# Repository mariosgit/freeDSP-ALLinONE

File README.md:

# freeDSP ALLinONE
BOARD STATUS: READY TO BE BUILT

Upgrade of the [freeDSP Classic SMD-B](https://github.com/freeDSP/freeDSP-CLASSIC-SMD-B/blob/master/README.md)

LICENCE: Creative Commons Attribution Share-Alike 4.0 license

https://freedsp.github.io/

[Mouser BOM](https://www.mouser.com/ProjectManager/ProjectDetail.aspx?AccessID=5c5f7288d7)

## mb/improvements branch

 * PowerDown muting, implemented with one 7414 gate and a Pot. The Pot must be fully turned up (cw) and then down until the mute LED turns of. This determines the Vin voltage where the shutdown occures, it should be slightly below the supply voltage but higher then 5V because @5V the Amps will go into power fail and that will hard click. [simulation](https://www.falstad.com/circuit/circuitjs.html?ctz=CQAgjCAMB0l3BWEAmM0EE4DMGAcB2ZLMSANjABYxkQFTbbJaBTAWjDACgA3EV-XBXCkmrQbmFMmEElOgQpUdJwBKfcZPUZ6YEVHAppNavpgJOAB3W6UyIWJvJcErKc5hcr1lgTH89VmRCcH9TdHBoUnosaCxXJEh3Tz4fGm0+ILT6OSQ0KJAYuIZEjy9UkAo4DODKxTMI-ML4qE4Adz4wUJt2ExtE9sC7YQ6u7M4AcxH6XFFO+nSpTgBjKeH2UJn9ZDYJCmgMASxPQWQ8OiclOC4AJ1XWCgl1nWzweDg21bn1aVDE26eQgEvnZFLJ4MtViDVlhIEImNsxBV9lgHnhnARSMhThhLpAuJMATD7F8sMg6h9BkIoQCof1IZUOiZaRSvl9AsEvnTKWtyn0KbyAuUFpZqjRaqKKqQhK5FlYemKqvLJdK3ANMiB0uzjBcuerqI9eTr+b5wBdvCbORSsVSGeaaMyBuVqeVxYkyfgOvRXQUsF6QABbACuABdmJx3RK2WSJJQhEIAIL+iysAD0AFEAHLhyAehzPUTOJgPCogABqAEsAHYACmogQopYAlNnc4R4bbMUIOGKAwBDCwAHQAzkPAxYLAAbACew9Lw+DAHthwhSxTcI4hnnNH8+G2ULa90T9DN3gTD7Dd2SClfFgM99TSHR97K+I-6A+n0eZS1SnwEKFqQodJaSUXJImiWJmi5e9IEee8GUSOUgPfW1kIqKpv11IYj0JC8sKpYJuWZX97lJPhiztciJByBoIKKBIRSValuwKC9MONGh7keNliy5CgyMAsiuJaAY2X1O5eM4AATCVxXYDAFXhEApOYAAzXtAwnYNpNkzUwAUipgOUtSNK0lkTDk-TFJEjoDMsuzhQGfixU1ZznxaOUpSo19pRodiBi84SAWEt0czucSgt0IsQAABQXVpmGuAB5SsWxSE0gpw9IhAAK0DIdg2HXthwAC2YCcLES+clyHcZmEKodClXCNWH-FDRF8GNQiEct-X9ZgpPLXtQ2HCx4qqocpPiythxU0MlmDcsF1SlqrMMgJNgQCg4xAJKVGHBdVNG8brim1oZqHAAfY6EuuMc0uCijNlYbKQCHCd4puiax1m+rmAWpbUv+N93NagCENed4nOA1CBIQ9xMU9dDZi9TYaBU9TNODVgJwGgwFEufEkYeFH1rcf4bEsiyqiYBAofIsi0K1MnoKvFj+EEcATGgzn2YELs9BKfB7D3PnSBjAyIDp+BLgwKg3gV+AaBUZgh3LAre0rJYwzvcXNA5gXFha9U5OjAoTSECwq1IYcq2HVTrmYAahwsTgF0Ma99AAD3XPEaASeR9CQJAJFQIO-yEBACaQCh330EhaD86iGECLA3YqPyaCYH2SCZOQZBLBJzfj8ixW-JBvDLgpLgYoA)
 * One of the 7414 was redundand and has been removed.
 * One of the clip adjust pots was redundand and has been removed.
 * 5V Arduino port was removed, use a 3.3 V device, i2C on the freedsp and adau headers.
 * Added a MCP23008 to read status and provide mute and spdif switching control. Can be left out.
 * I had problems with the ADAU onboard voltage regulator, replaced it with a linear regulator. (dropout is 1.2V should be ok to run @ 3.3V) Anyway increased the switched reg to 5V and the 3.3V line runs on another 1117.
 * Ferritbead before the AMP chips is wrong, AMPs are now powered by VIN.
 * Removed Power input from USBi port.
 * JumperWire and solder enforceable power traces between amps and power terminal
 * break out gain config pins - add 1k resistors r49 r50 as needed.

##### CanDo ?

 * Replace CS8422 QFPpamp / Outdated. But it's the only one with integrated SRC :( 
 * Replace 1206 parts with std 603 parts.
 * Use a power management/supervisor chipo for mute ? 
   * TPS3840PH49DBVR ? ActHigh not adjustable, max 12v
   * TL7700 - active low
   * TPS38 - availables are active low.
   * TL7733 - max 20V, act low+high
   * aaahhh

## About

The freeDSP is an open-source digital signal processor family for the do-it-yourself community. The applications range from active loudspeaker concepts (digital crossovers, bass enhancement, ...) and room equalization over advanced musical effect processors to car audio signal processing. 

The _freeDSP ALLinONE_ is an all-in-one version of the original _freeDSP Classic SMD-B_ with a few improvements, upgrades and changes.
It features four amplified analog outputs as well as S/PDIF in- and output (optical and RCA).
This board has been designed using the Cross-Platform Open Source Tool [KiCad](http://kicad.org/).

More informations kann be found on the [freeDSP website](http://freedsp.cc)

You can find a PDF version of the schematic in the SOURCES folder (LINK)

## Links

[freeDSP Website](http://freedsp.cc)

[Documentation in Google Doc](https://docs.google.com/document/d/1258PKKEvrk1GpFIaAHhm8G6f0HHNBfSL8KVq2VGgUKc/edit?usp=sharing)

[freeDSP Guidelines](https://github.com/freeDSP/WIKI-AND-GENERAL-TOPICS/wiki/freeDSP-Guidelines)

## Git usage

#### How to setup local repository
- Change to your FreeDSP directory
- Clone the repository (including submodule)  
 `git clone --recursive https://github.com/freeDSP/freeDSP-ALLinONE.git` 
- Change to the newly created ALLinONE directory
- Checkout a branch for the library submodule, if you want to modify it as well
  `git submodule foreach 'git checkout 'master''`
- Open the project file in KiCad

#### How to update the local copy
- To update the project  
  `git pull`
- To update the library  
  `git submodule update --remote --merge`

#### To commit and push local changes
- If you modified something in the LIBRARY folder, change to the LIBRARY folder and run  
  `git add .` (Only required if files were added)  
  `git commit -am "Message"`  (Describe what you changed)  
- Change to the project root directory and run
  `git add .` (Only required if files were added)  
  `git commit -am "Message"`  (Describe what you changed)    
- In the project directory run  
  `git push --recurse-submodule=on-demand`  

#### Define alias to make things shorter
- In the project directory run
  `git config alias.supdate 'submodule update --remote --merge'`  
  `git config alias.spush 'push --recurse-submodules=on-demand'`  
- Afterwards you can use `git supdate` to update the submodule and `git spush` to push any commited changes  

#### Other useful commands
- `git status`  
  Shows general information about the current branch, uncommited changes, not yet added new files and more
- `git diff`  
  Shows uncommited changes
- `git reset --hard origin/master`
  Reset all files to the current status of the dev-hs-01 branch on the Github repository  
  **Careful** This deletes all local changes, so make sure all changes you made and you do not want to delete are pushed to the remote repository

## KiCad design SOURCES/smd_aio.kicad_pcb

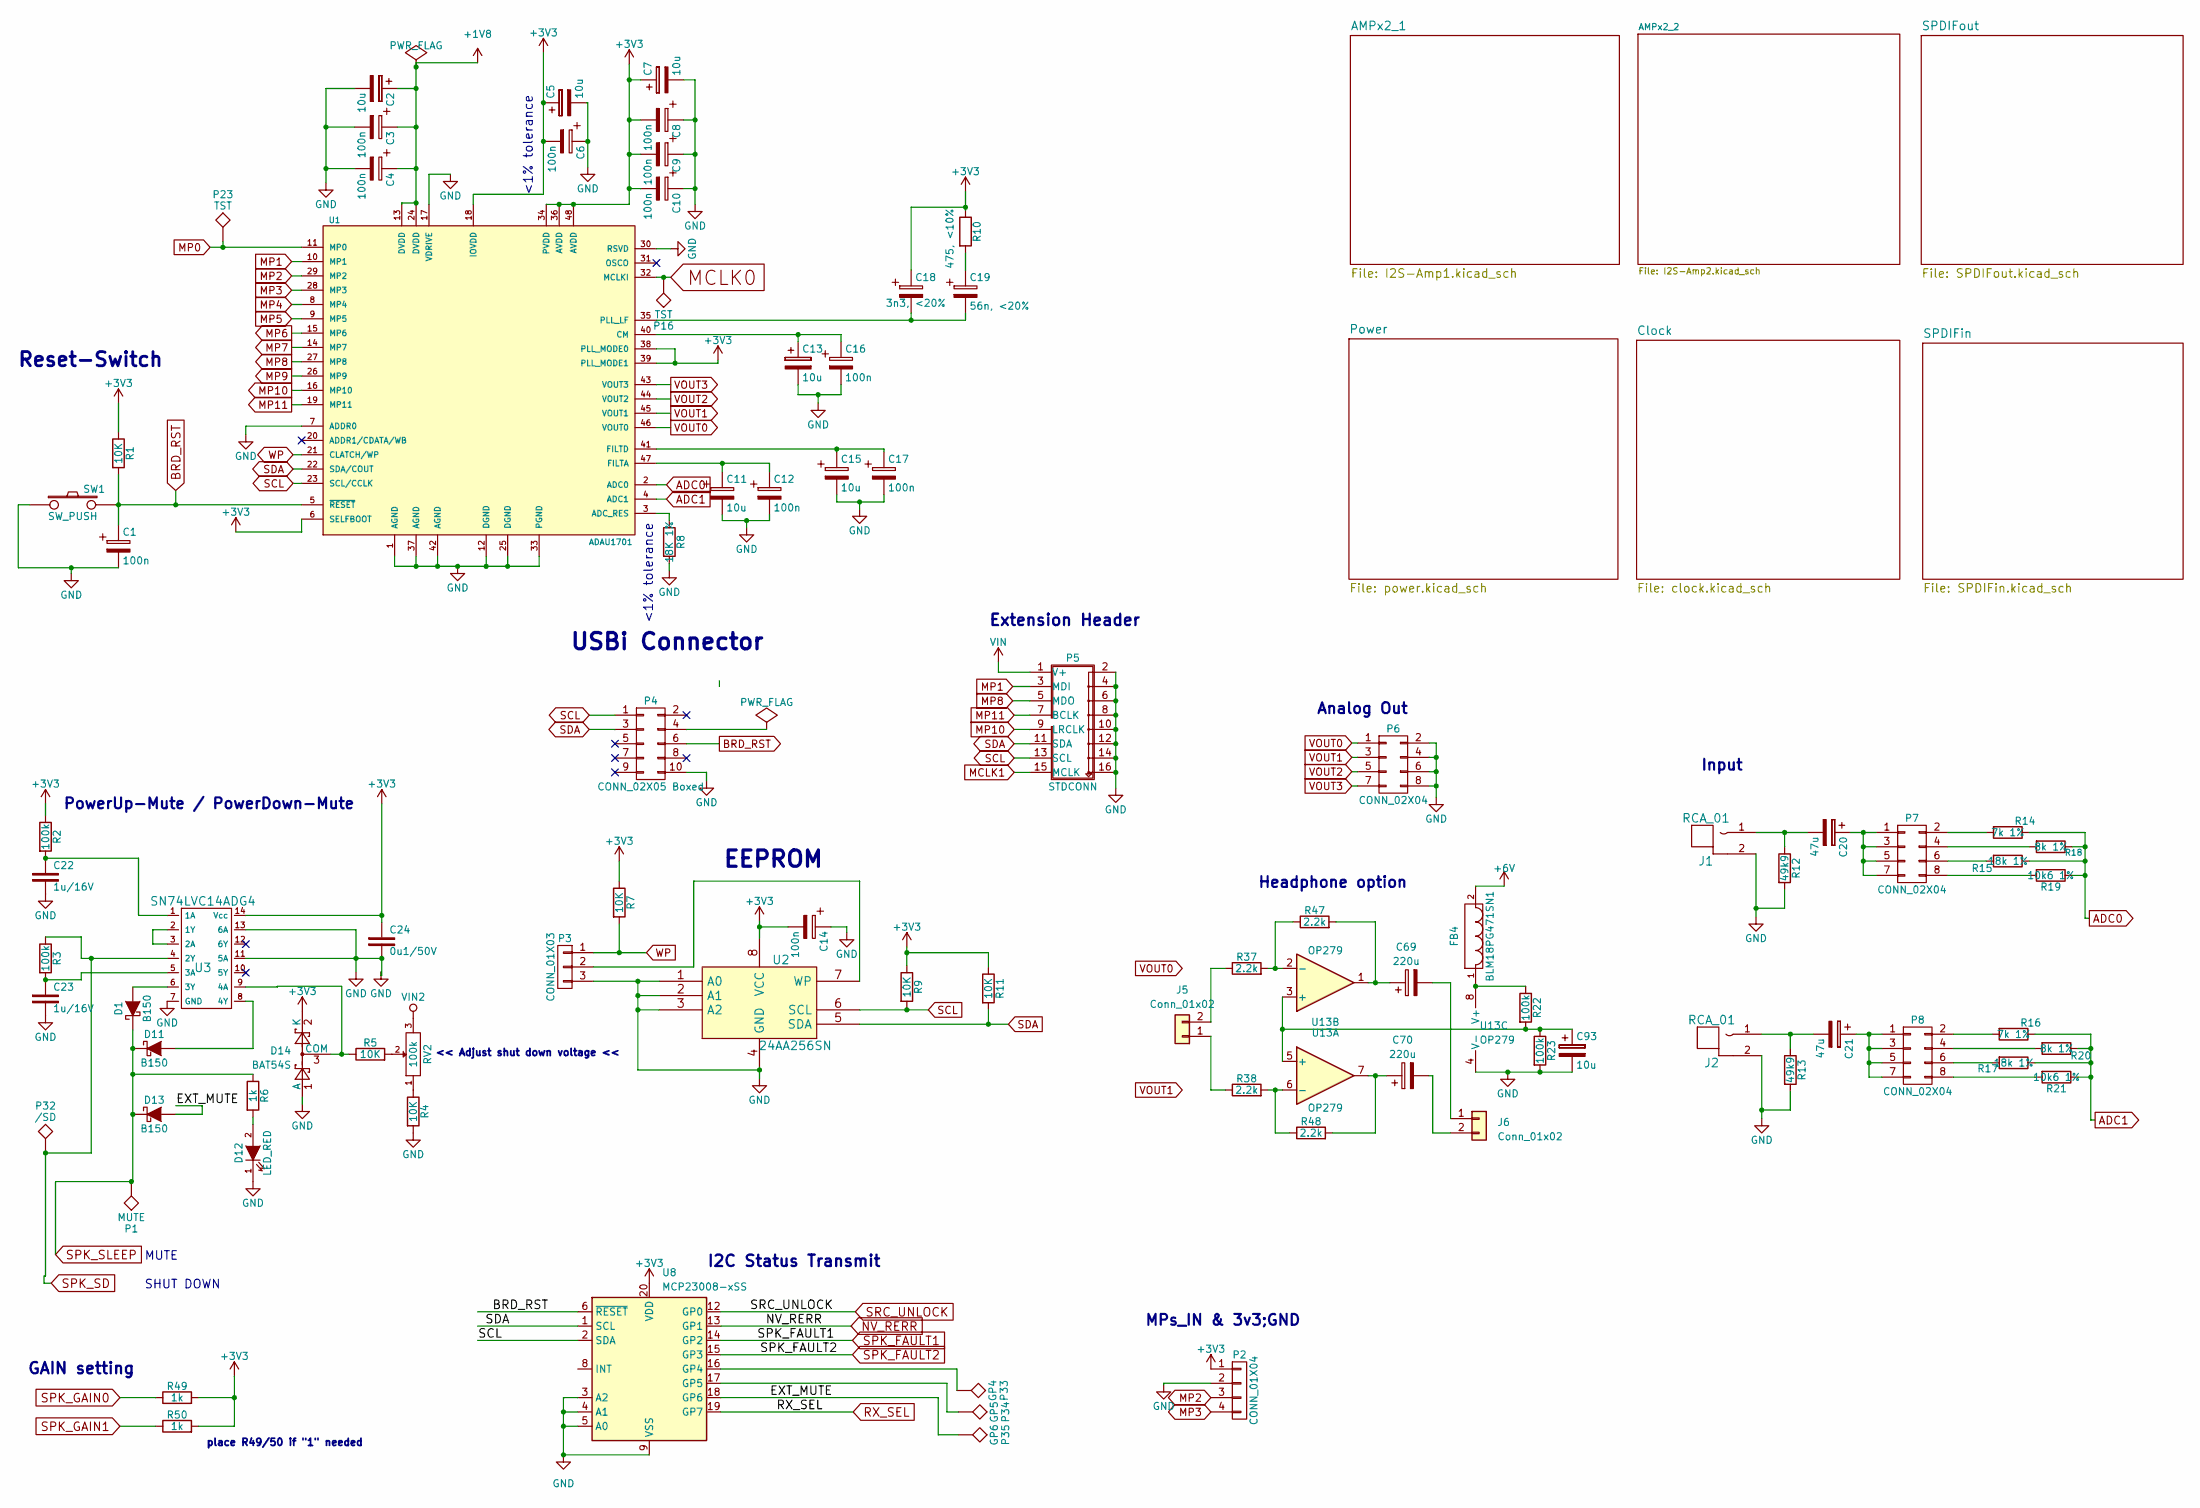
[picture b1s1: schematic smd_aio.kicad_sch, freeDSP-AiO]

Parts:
C1, C3, C4, C6, C8, C9, C10, C12, C14, C16, C17: 100n; C_1206_HandSoldering
C2: 10u; C_1210_3225Metric_Pad1.33x2.70mm_HandSolder
C5, C7, C13, C93: 10u; C_Radial_D5_L11_P2
C11, C15: 10u; C_1206_HandSoldering
C18: 3n3, <20%; C_1206_HandSoldering
C19: 56n, <20%; C_1206_HandSoldering
C20, C21: 47u; C_Radial_D5_L11_P2
C22, C23: 1u/16V; C_1206_HandSoldering
C24: 0u1/50V; C_1206_HandSoldering
C69, C70: 220u; CP_Elec_6.3x5.9
D1, D11, D13: B150; SMA
D12: LED_RED; R_1206_HandSoldering
D14: BAT54S; SOT-23
FB4: BLM18PG471SN1; R_0603_HandSoldering
J1, J2: RCA_01; RCA_RCJ-01x
J5, J6: Conn_01x02; PinHeader_1x02_P2.54mm_Vertical
P1: MUTE; Measurement_Point_Round-SMD-Pad_Small
P2: CONN_01X04; Pin_Header_Straight_1x04
P3: CONN_01X03; Pin_Header_Straight_1x03
P4: CONN_02X05 Boxed; IDC_Header_Straight_10pins
P5: STDCONN; IDC_Header_Straight_16pins
P6, P7, P8: CONN_02X04; Pin_Header_Straight_2x04
P16, P23: TST; Measurement_Point_Round-SMD-Pad_Small
P32: /SD; Measurement_Point_Round-SMD-Pad_Small
P33: GP4; Measurement_Point_Round-SMD-Pad_Small
P34: GP5; Measurement_Point_Round-SMD-Pad_Small
P35: GP6; Measurement_Point_Round-SMD-Pad_Small
R1, R4, R5, R7, R9, R11: 10K; R_1206_HandSoldering
R2, R3: 100k; R_1206_HandSoldering
R6: 1k; R_1206_HandSoldering
R8: 18K 1%; R_1206_HandSoldering
R10: 475, <10%; R_1206_HandSoldering
R12, R13: 49k9; R_1206_HandSoldering
R14, R16: 7k 1%; R_1206_HandSoldering
R15, R17: 18k 1%; R_1206_HandSoldering
R18, R20: 8k 1%; R_1206_HandSoldering
R19, R21: 10k6 1%; R_1206_HandSoldering
R22, R23: 100k; R_0603_HandSoldering
R37, R38, R47, R48: 2.2k; R_0603_HandSoldering
R49, R50: 1k; R_0603_1608Metric_Pad0.98x0.95mm_HandSolder
RV2: 100k; M64Z104KB40
SW1: SW_PUSH; SW_PUSH_6mm
U1: ADAU1701; LQFP-48_7x7mm_Pitch0.5mm
U2: 24AA256SN; SOIC-8_3.9x4.9mm_Pitch1.27mm
U3: SN74LVC14ADG4; SOIC-14_3.9x8.7mm_Pitch1.27mm
U8: MCP23008-xSS; SSOP-20_5.3x7.2mm_P0.65mm
U13: OP279; SO-8_3.9x4.9mm_P1.27mm

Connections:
+1V8: C2.1, C3.1, C4.1, U1.13 (DVDD), U1.24 (DVDD); also elsewhere on the board
+3V3: C5.1, C6.2, C7.1, C8.2, C9.2, C10.2, C14.2, C18.1, C24.1, D14.2 (K), P2.1, R1.1, R2.1, R7.1, R9.1, R10.1, R11.1, R49.2, R50.2, U1.6 (SELFBOOT), U1.18 (IOVDD), U1.34 (PVDD), U1.36 (AVDD), U1.38 (PLL_MODE0), U1.39 (PLL_MODE1), U1.48 (AVDD), U2.8 (VCC), U3.14 (Vcc), U8.20 (VDD); also elsewhere on the board
+6V: FB4.2; also elsewhere on the board
/EXT_MUTE: D13.2 (A), P35.1, U8.18 (GP6)
ADC0: R14.1, R15.1, R18.1, R19.1, U1.2 (ADC0)
ADC1: R16.1, R17.1, R20.1, R21.1, U1.4 (ADC1)
BRD_RST: C1.1, P4.6, R1.2, SW1.2, U1.5 (~RESET), U8.6 (~RESET); also elsewhere on the board
GND: C1.2, C2.2, C3.2, C4.2, C5.2, C6.1, C7.2, C8.1, C9.1, C10.1, C11.2, C12.2, C13.2, C14.1, C15.2, C16.2, C17.2, C22.2, C23.2, C24.2, C93.2, D12.1 (K), D14.1 (A), J1.2 (GND), J2.2 (GND), P2.2, P3.3, P4.10, P5.2 (GND), P5.4 (GND), P5.6 (GND), P5.8 (GND), P5.10 (GND), P5.12 (GND), P5.14 (GND), P5.16 (GND), P6.2, P6.4, P6.6, P6.8, R4.2, R8.2, R12.2, R13.2, R23.2, SW1.1, U1.1 (AGND), U1.7 (ADDR0), U1.12 (DGND), U1.17 (VDRIVE), U1.25 (DGND), U1.30 (RSVD), U1.33 (PGND), U1.37 (AGND), U1.42 (AGND), U2.1 (A0), U2.2 (A1), U2.3 (A2), U2.4 (GND), U3.7 (GND), U3.11 (5A), U3.13 (6A), U8.3 (A2), U8.4 (A1), U8.5 (A0), U8.9 (VSS), U13.4 (V-); also elsewhere on the board
MCLK0: P16.1, U1.32 (MCLKI); also elsewhere on the board
MCLK1: P5.15 (MCLK); also elsewhere on the board
MP0: P23.1, U1.11 (MP0); also elsewhere on the board
MP1: P5.3 (MDI), U1.10 (MP1)
MP2: P2.3, U1.29 (MP2)
MP3: P2.4, U1.28 (MP3)
MP4: U1.8 (MP4); also elsewhere on the board
MP5: U1.9 (MP5); also elsewhere on the board
MP6: U1.15 (MP6); also elsewhere on the board
MP7: U1.14 (MP7); also elsewhere on the board
MP8: P5.5 (MDO), U1.27 (MP8)
MP9: U1.26 (MP9); also elsewhere on the board
MP10: P5.9 (LRCLK), U1.16 (MP10); also elsewhere on the board
MP11: P5.7 (BCLK), U1.19 (MP11); also elsewhere on the board
NV_RERR: U8.13 (GP1); also elsewhere on the board
unnamed: C19.1, R10.2
unnamed: C69.1, R47.2, U13.1
unnamed: C70.1, R48.2, U13.7
unnamed: D1.2 (A), U3.6 (3Y)
unnamed: D11.2 (A), U3.8 (4Y)
unnamed: D12.2 (A), R6.2
unnamed: D14.3 (COM), R5.1, U3.9 (4A)
unnamed: C20.2, J1.1 (SIG), R12.1
unnamed: C21.2, J2.1 (SIG), R13.1
unnamed: J5.1, R38.1
unnamed: J5.2, R37.1
unnamed: C69.2, J6.1
unnamed: C70.2, J6.2
unnamed: P3.2, U2.7 (WP)
unnamed: C20.1, P7.1, P7.3, P7.5, P7.7
unnamed: P7.2, R14.2
unnamed: P7.4, R18.2
unnamed: P7.6, R15.2
unnamed: P7.8, R19.2
unnamed: C21.1, P8.1, P8.3, P8.5, P8.7
unnamed: P8.2, R16.2
unnamed: P8.4, R20.2
unnamed: P8.6, R17.2
unnamed: P8.8, R21.2
unnamed: R4.1, RV2.1
unnamed: R5.2, RV2.2
unnamed: R8.1, U1.3 (ADC_RES)
unnamed: C13.1, C16.1, U1.40 (CM)
unnamed: C11.1, C12.1, U1.47 (FILTA)
unnamed: C15.1, C17.1, U1.41 (FILTD)
unnamed: C18.2, C19.2, U1.35 (PLL_LF)
unnamed: C22.1, R2.2, U3.1 (1A)
unnamed: U3.2 (1Y), U3.3 (2A)
unnamed: C23.1, R3.2, U3.5 (3A)
unnamed: P33.1, U8.16 (GP4)
unnamed: P34.1, U8.17 (GP5)
unnamed: C93.1, R22.2, R23.1, U13.3 (+), U13.5 (+)
unnamed: R37.2, R47.1, U13.2 (-)
unnamed: R38.2, R48.1, U13.6 (-)
unnamed: FB4.1, R22.1, U13.8 (V+)
RX_SEL: U8.19 (GP7); also elsewhere on the board
SCL: P4.1, P5.13 (SCL), R9.2, U1.23 (SCL/CCLK), U2.6 (SCL), U8.2 (SDA)
SDA: P4.3, P5.11 (SDA), R11.2, U1.22 (SDA/COUT), U2.5 (SDA), U8.1 (SCL)
SPK_FAULT1: U8.14 (GP2); also elsewhere on the board
SPK_FAULT2: U8.15 (GP3); also elsewhere on the board
SPK_GAIN0: R49.1; also elsewhere on the board
SPK_GAIN1: R50.1; also elsewhere on the board
SPK_SD: P32.1, R3.1, U3.4 (2Y); also elsewhere on the board
SPK_SLEEP: D1.1 (K), D11.1 (K), D13.1 (K), P1.1, R6.1; also elsewhere on the board
SRC_UNLOCK: U8.12 (GP0); also elsewhere on the board
VIN: P5.1 (V+); also elsewhere on the board
VIN2: RV2.3; also elsewhere on the board
VOUT0: P6.1, U1.46 (VOUT0)
VOUT1: P6.3, U1.45 (VOUT1)
VOUT2: P6.5, U1.44 (VOUT2)
VOUT3: P6.7, U1.43 (VOUT3)
WP: P3.1, R7.2, U1.21 (CLATCH/WP)

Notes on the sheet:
MPs_IN & 3v3;GND
Headphone option
PowerUp-Mute / PowerDown-Mute
I2C Status Transmit
MUTE
Extension Header
Analog Out
USBi Connector
place R49/50 if "1" needed
GAIN setting
<< Adjust shut down voltage <<
SHUT DOWN
Reset-Switch
Input
<1% tolerance
EEPROM

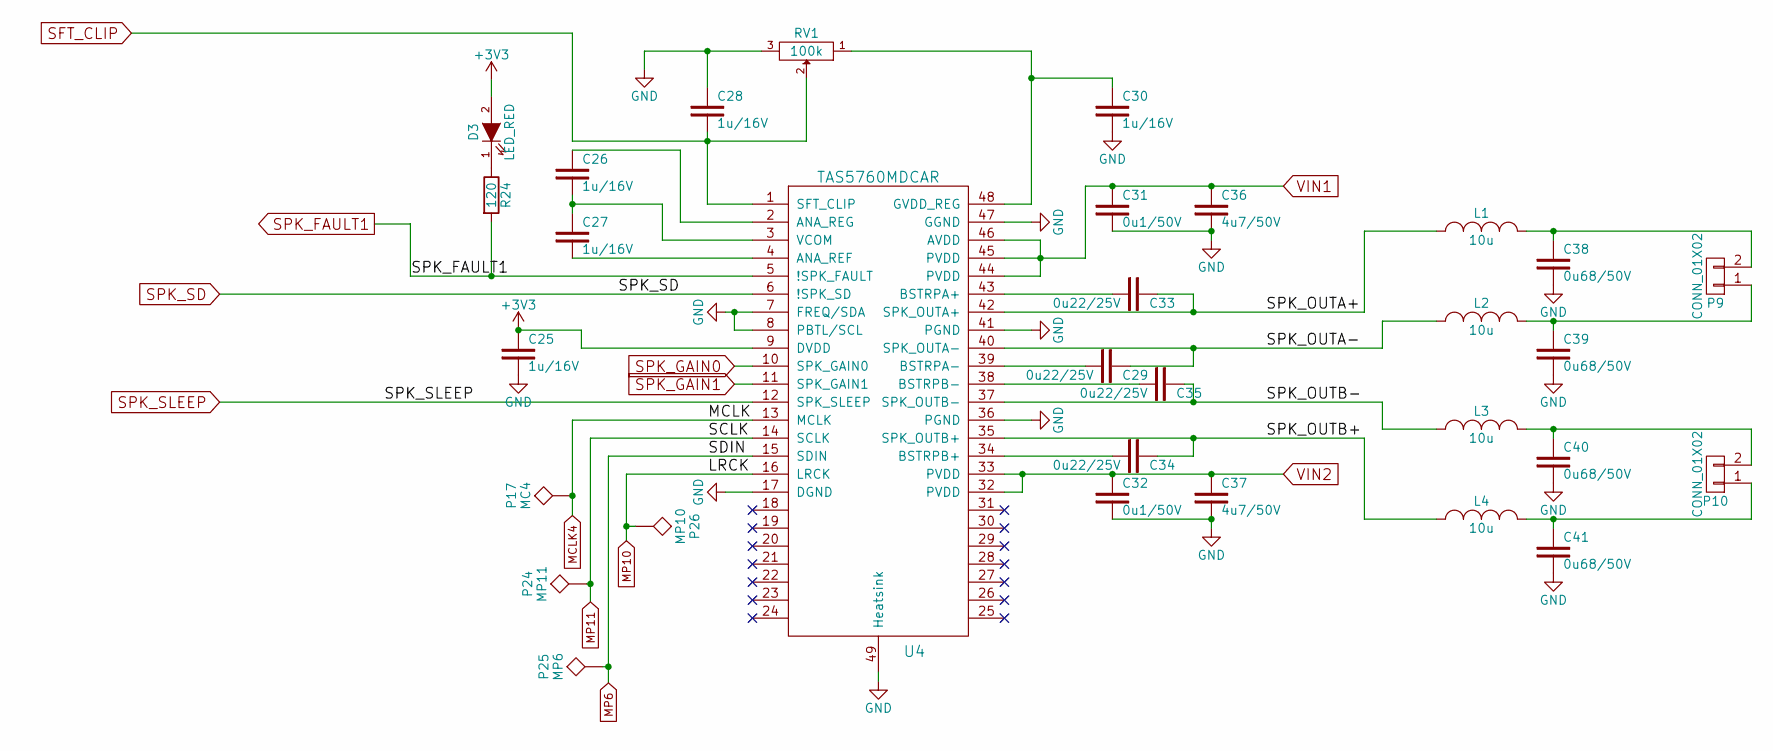
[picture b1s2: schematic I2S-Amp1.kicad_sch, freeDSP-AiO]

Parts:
C25, C26, C27, C28, C30: 1u/16V; C_1206_HandSoldering
C29, C33, C34, C35: 0u22/25V; C_0805_HandSoldering
C31, C32: 0u1/50V; C_1206_HandSoldering
C36, C37: 4u7/50V; C_1206_HandSoldering
C38, C39, C40, C41: 0u68/50V; C_1206_HandSoldering
D3: LED_RED; R_1206_HandSoldering
L1, L2, L3, L4: 10u; 1D10ASeries
P9, P10: CONN_01X02; RIACON101-2
P17: MC4; Measurement_Point_Round-SMD-Pad_Small
P24: MP11; Measurement_Point_Round-SMD-Pad_Small
P25: MP6; Measurement_Point_Round-SMD-Pad_Small
P26: MP10; Measurement_Point_Round-SMD-Pad_Small
R24: 120; R_1206_HandSoldering
RV1: 100k; M64Z104KB40
U4: TAS5760MDCAR; HTSSOP-48

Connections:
+3V3: C25.1, D3.2 (A), U4.9 (DVDD); also elsewhere on the board
/AMPx2_1/SPK_OUTA+: C33.1, L1.1, U4.42 (SPK_OUTA+)
/AMPx2_1/SPK_OUTA-: C29.1, L2.1, U4.40 (SPK_OUTA-)
/AMPx2_1/SPK_OUTB+: C34.1, L4.1, U4.35 (SPK_OUTB+)
/AMPx2_1/SPK_OUTB-: C35.1, L3.1, U4.37 (SPK_OUTB-)
GND: C25.2, C28.1, C30.2, C31.2, C32.2, C36.2, C37.2, C38.2, C39.2, C40.2, C41.2, RV1.3, U4.7 (FREQ/SDA), U4.8 (PBTL/SCL), U4.17 (DGND), U4.36 (PGND), U4.41 (PGND), U4.47 (GGND), U4.49 (Heatsink); also elsewhere on the board
MCLK4: P17.1, U4.13 (MCLK); also elsewhere on the board
MP6: P25.1, U4.15 (SDIN); also elsewhere on the board
MP10: P26.1, U4.16 (LRCK); also elsewhere on the board
MP11: P24.1, U4.14 (SCLK); also elsewhere on the board
unnamed: D3.1 (K), R24.1
unnamed: C39.1, L2.2, P9.1
unnamed: C38.1, L1.2, P9.2
unnamed: C41.1, L4.2, P10.1
unnamed: C40.1, L3.2, P10.2
unnamed: C27.2, U4.4 (ANA_REF)
unnamed: C26.1, U4.2 (ANA_REG)
unnamed: C33.2, U4.43 (BSTRPA+)
unnamed: C29.2, U4.39 (BSTRPA-)
unnamed: C34.2, U4.34 (BSTRPB+)
unnamed: C35.2, U4.38 (BSTRPB-)
unnamed: C30.1, RV1.1, U4.48 (GVDD_REG)
unnamed: C26.2, C27.1, U4.3 (VCOM)
SFT_CLIP: C28.2, RV1.2, U4.1 (SFT_CLIP); also elsewhere on the board
SPK_FAULT1: R24.2, U4.5 (!SPK_FAULT); also elsewhere on the board
SPK_GAIN0: U4.10 (SPK_GAIN0); also elsewhere on the board
SPK_GAIN1: U4.11 (SPK_GAIN1); also elsewhere on the board
SPK_SD: U4.6 (!SPK_SD); also elsewhere on the board
SPK_SLEEP: U4.12 (SPK_SLEEP); also elsewhere on the board
VIN1: C31.1, C36.1, U4.44 (PVDD), U4.45 (PVDD), U4.46 (AVDD); also elsewhere on the board
VIN2: C32.1, C37.1, U4.32 (PVDD), U4.33 (PVDD); also elsewhere on the board

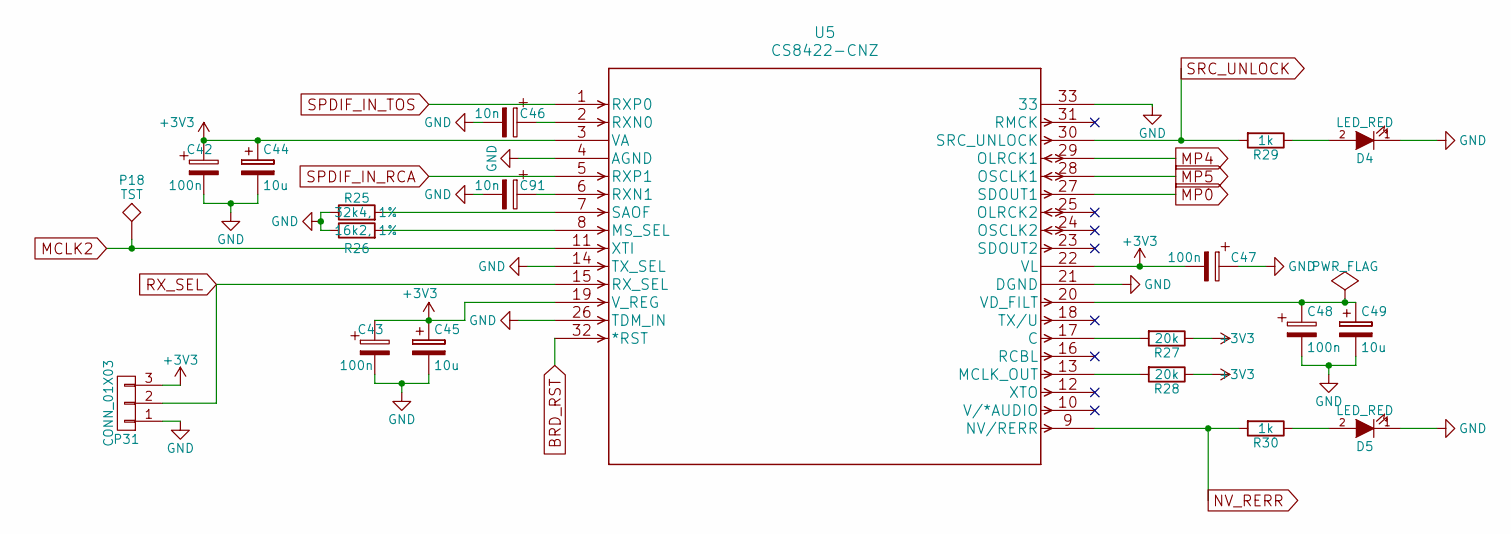
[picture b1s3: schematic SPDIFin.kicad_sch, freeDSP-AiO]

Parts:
C42, C43, C47, C48: 100n; C_1206_HandSoldering
C44, C45, C49: 10u; C_Radial_D5_L11_P2
C46, C91: 10n; C_1206_HandSoldering
D4, D5: LED_RED; R_1206_HandSoldering
P18: TST; Measurement_Point_Round-SMD-Pad_Small
P31: CONN_01X03; Pin_Header_Straight_1x03
R25: 32k4, 1%; R_1206_HandSoldering
R26: 16k2, 1%; R_1206_HandSoldering
R27, R28: 20k; R_1206_HandSoldering
R29, R30: 1k; R_1206_HandSoldering
U5: CS8422-CNZ

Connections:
+3V3: C42.1, C43.1, C44.1, C45.1, C47.2, P31.3, R27.1, R28.1, U5.3 (VA), U5.19 (V_REG), U5.22 (VL); also elsewhere on the board
BRD_RST: U5.32 (*RST); also elsewhere on the board
GND: C42.2, C43.2, C44.2, C45.2, C46.2, C47.1, C48.2, C49.2, C91.2, D4.1 (K), D5.1 (K), P31.1, R25.1, R26.1, U5.4 (AGND), U5.14 (TX_SEL), U5.21 (DGND), U5.26 (TDM_IN), U5.33; also elsewhere on the board
MCLK2: P18.1, U5.11 (XTI); also elsewhere on the board
MP0: U5.27 (SDOUT1); also elsewhere on the board
MP4: U5.29 (OLRCK1); also elsewhere on the board
MP5: U5.28 (OSCLK1); also elsewhere on the board
NV_RERR: R30.2, U5.9 (NV/RERR); also elsewhere on the board
unnamed: D4.2 (A), R29.1
unnamed: D5.2 (A), R30.1
unnamed: R27.2, U5.17 (C)
unnamed: R28.2, U5.13 (MCLK_OUT)
unnamed: R26.2, U5.8 (MS_SEL)
unnamed: C46.1, U5.2 (RXN0)
unnamed: C91.1, U5.6 (RXN1)
unnamed: R25.2, U5.7 (SAOF)
unnamed: C48.1, C49.1, U5.20 (VD_FILT)
RX_SEL: P31.2, U5.15 (RX_SEL); also elsewhere on the board
SPDIF_IN_RCA: U5.5 (RXP1); also elsewhere on the board
SPDIF_IN_TOS: U5.1 (RXP0); also elsewhere on the board
SRC_UNLOCK: R29.2, U5.30 (SRC_UNLOCK); also elsewhere on the board

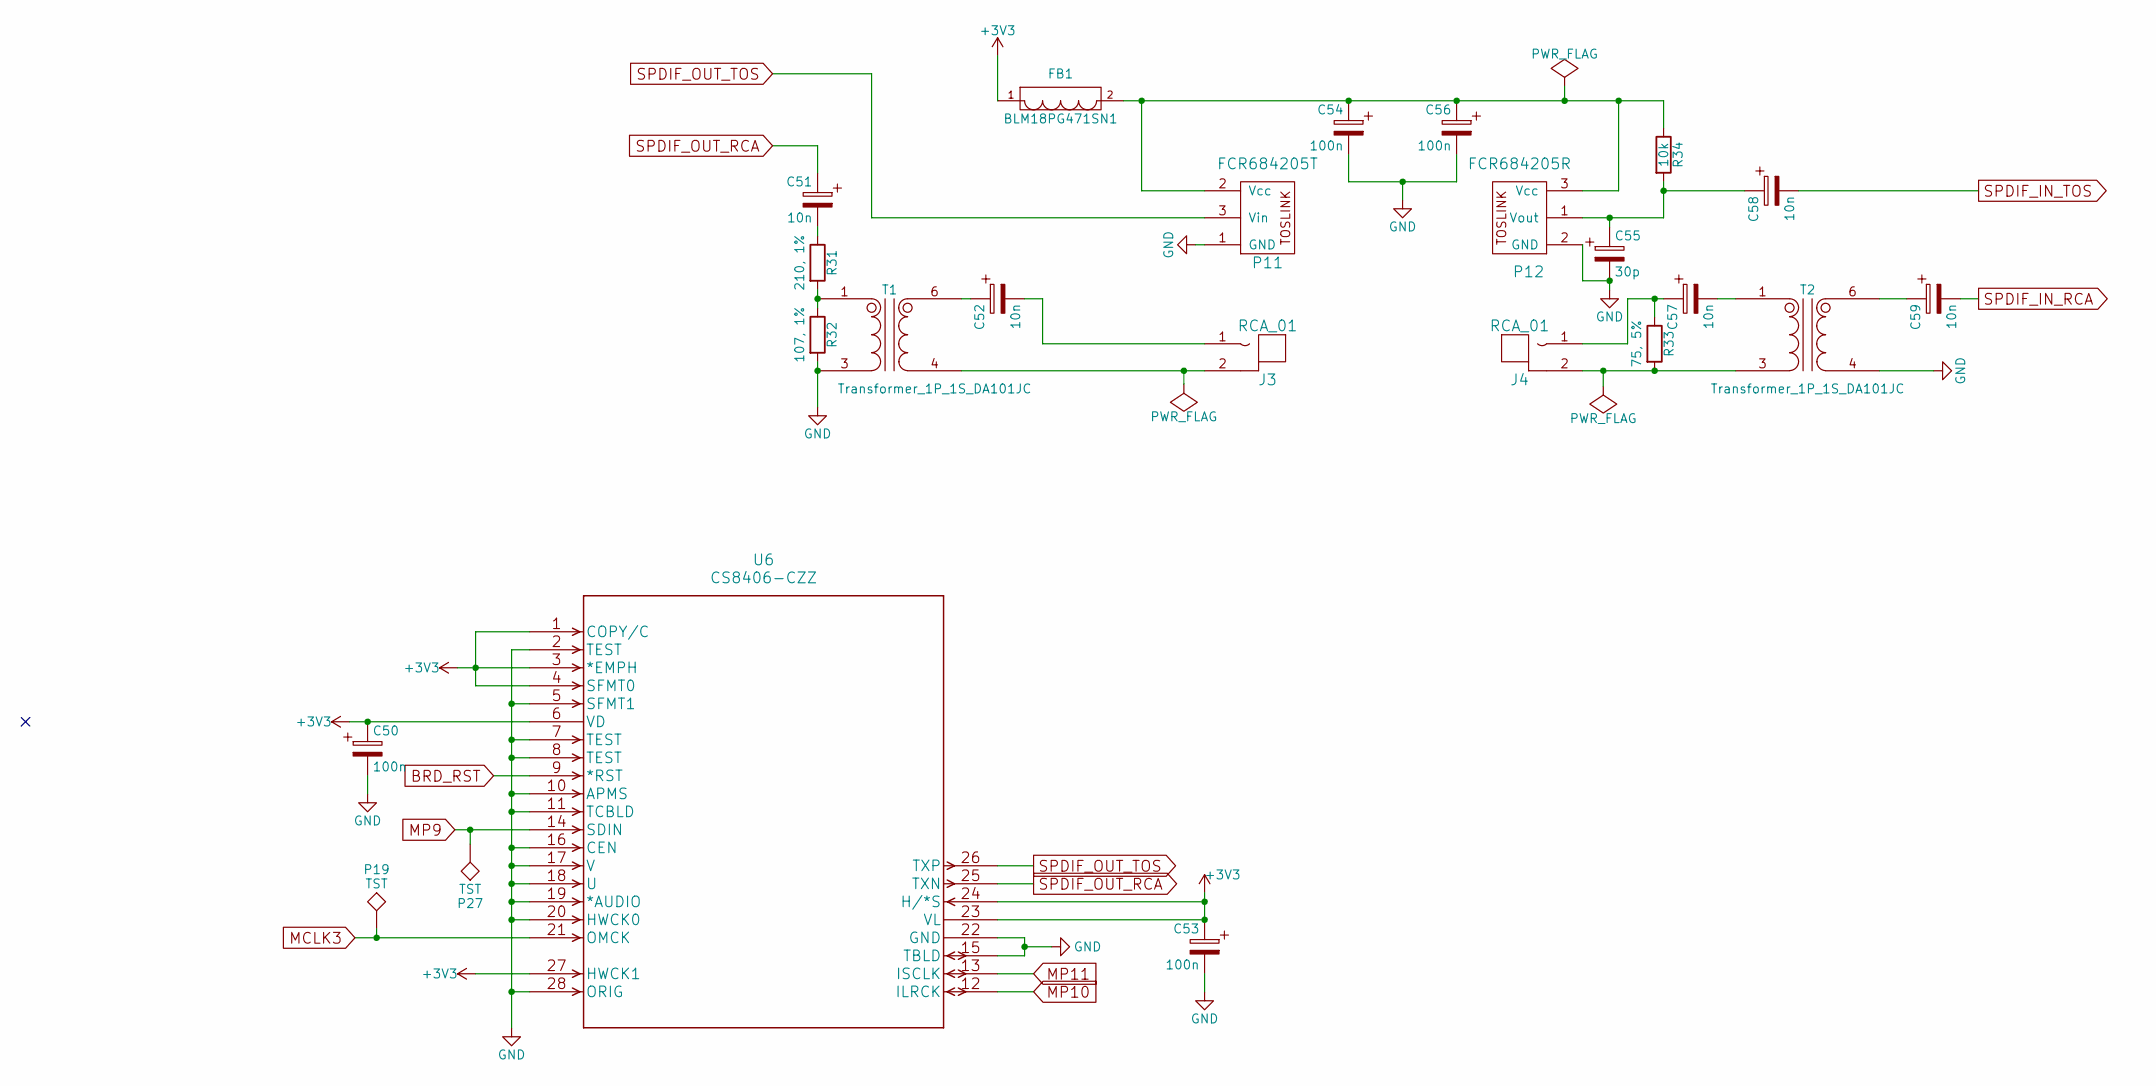
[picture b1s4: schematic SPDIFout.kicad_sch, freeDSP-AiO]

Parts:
C50, C53, C54, C56: 100n; C_1206_HandSoldering
C51, C52, C57, C58, C59: 10n; C_1206_HandSoldering
C55: 30p; C_1206_HandSoldering
FB1: BLM18PG471SN1; R_0603_HandSoldering
J3, J4: RCA_01; RCA_RCJ-01x
P11: FCR684205T; FC684205_R_T
P12: FCR684205R; FC684205_R_T
P19, P27: TST; Measurement_Point_Round-SMD-Pad_Small
R31: 210, 1%; R_1206_HandSoldering
R32: 107, 1%; R_1206_HandSoldering
R33: 75, 5%; R_1206_HandSoldering
R34: 10k; R_1206_HandSoldering
T1, T2: Transformer_1P_1S_DA101JC; DA101JC
U6: CS8406-CZZ

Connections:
+3V3: C50.1, C53.1, FB1.1, U6.1 (COPY/C), U6.3 (*EMPH), U6.4 (SFMT0), U6.6 (VD), U6.23 (VL), U6.24 (H/*S), U6.27 (HWCK1); also elsewhere on the board
BRD_RST: U6.9 (*RST); also elsewhere on the board
GND: C50.2, C53.2, C54.2, C55.2, C56.2, P11.1 (GND), P12.2 (GND), R32.2, T1.3 (SM), T2.4 (S1), U6.2 (TEST), U6.5 (SFMT1), U6.7 (TEST), U6.8 (TEST), U6.10 (APMS), U6.11 (TCBLD), U6.15 (TBLD), U6.16 (CEN), U6.17 (V), U6.18 (U), U6.19 (*AUDIO), U6.20 (HWCK0), U6.22 (GND), U6.28 (ORIG); also elsewhere on the board
MCLK3: P19.1, U6.21 (OMCK); also elsewhere on the board
MP9: P27.1, U6.14 (SDIN); also elsewhere on the board
MP10: U6.12 (ILRCK); also elsewhere on the board
MP11: U6.13 (ISCLK); also elsewhere on the board
unnamed: C51.2, R31.1
unnamed: J3.2 (GND), T1.4 (S1)
unnamed: C52.2, J3.1 (SIG)
unnamed: J4.2 (GND), R33.2, T2.3 (SM)
unnamed: C57.1, J4.1 (SIG), R33.1
unnamed: C54.1, C56.1, FB1.2, P11.2 (Vcc), P12.3 (Vcc), R34.1
unnamed: C55.1, C58.1, P12.1 (Vout), R34.2
unnamed: C52.1, T1.6 (PM)
unnamed: R31.2, R32.1, T1.1 (PR1)
unnamed: C59.1, T2.6 (PM)
unnamed: C57.2, T2.1 (PR1)
SPDIF_IN_RCA: C59.2; also elsewhere on the board
SPDIF_IN_TOS: C58.2; also elsewhere on the board
SPDIF_OUT_RCA: C51.1, U6.25 (TXN)
SPDIF_OUT_TOS: P11.3 (Vin), U6.26 (TXP)

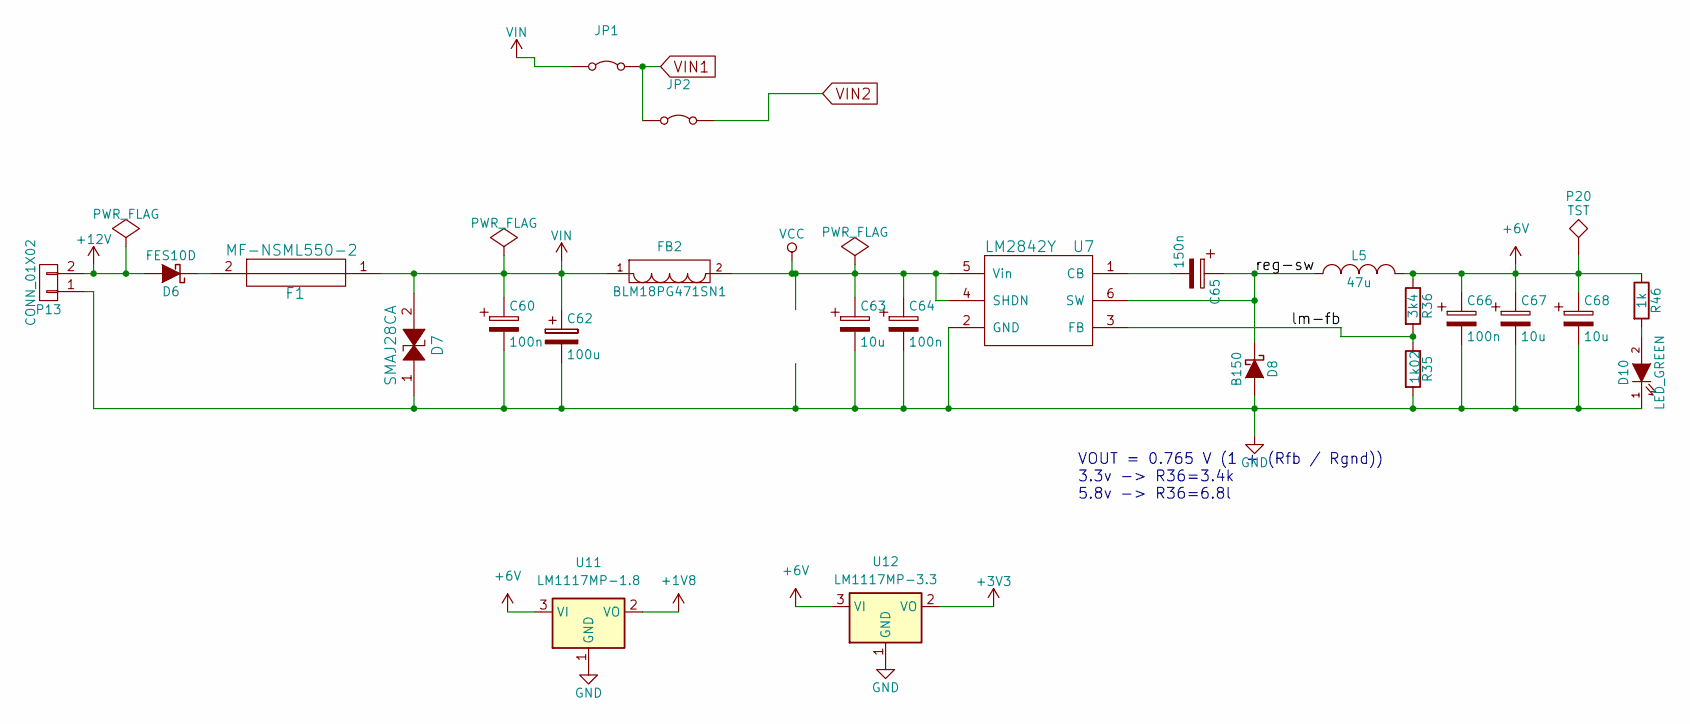
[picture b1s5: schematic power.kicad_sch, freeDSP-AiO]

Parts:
C60, C64, C66: 100n; C_1206_HandSoldering
C62: 100u; C_Radial_D6.3_L11.2_P2.5
C63, C67, C68: 10u; C_1206_HandSoldering
C65: 150n; C_1206_HandSoldering
D6: FES10D
D7: SMAJ28CA; SMA
D8: B150; SMA
D10: LED_GREEN; R_1206_HandSoldering
F1: MF-NSML550-2; R_1206_HandSoldering
FB2: BLM18PG471SN1; R_0603_HandSoldering
JP1, JP2: Jumper_2_Bridged; Jumper-Wire_25mm_Blue
L5: 47u; Choke_SMD_10.1x10.0
P13: CONN_01X02; RIACON101-2
P20: TST; Measurement_Point_Round-SMD-Pad_Small
R35: 1k02; R_1206_HandSoldering
R36: 3k4; R_1206_HandSoldering
R46: 1k; R_1206_HandSoldering
U7: LM2842Y; SOT23-6_1.7x3.0mm_Pitch0.95mm
U11: LM1117MP-1.8; SOT-223-3_TabPin2
U12: LM1117MP-3.3; SOT-223-3_TabPin2

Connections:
+1V8: U11.2 (VO); also elsewhere on the board
+3V3: U12.2 (VO); also elsewhere on the board
+6V: C66.1, C67.1, C68.1, L5.2, P20.1, R36.1, R46.1, U11.3 (VI), U12.3 (VI); also elsewhere on the board
+12V: D6.2 (A), P13.2
/Power/lm-fb: R35.1, R36.2, U7.3 (FB)
/Power/reg-sw: C65.1, D8.1 (K), L5.1, U7.6 (SW)
GND: C60.2, C62.2, C63.2, C64.2, C66.2, C67.2, C68.2, D7.1, D8.2 (A), D10.1 (K), P13.1, R35.2, U7.2 (GND), U11.1 (GND), U12.1 (GND); also elsewhere on the board
unnamed: D6.1 (K), F1.2
unnamed: D10.2 (A), R46.2
unnamed: C65.2, U7.1 (CB)
VCC: C63.1, C64.1, FB2.2, U7.4 (SHDN), U7.5 (Vin)
VIN: C60.1, C62.1, D7.2, F1.1, FB2.1, JP1.1 (A); also elsewhere on the board
VIN1: JP1.2 (B), JP2.1 (A); also elsewhere on the board
VIN2: JP2.2 (B); also elsewhere on the board

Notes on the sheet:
VOUT = 0.765 V (1 + (Rfb / Rgnd)) 3.3v -> R36=3.4k 5.8v -> R36=6.8l

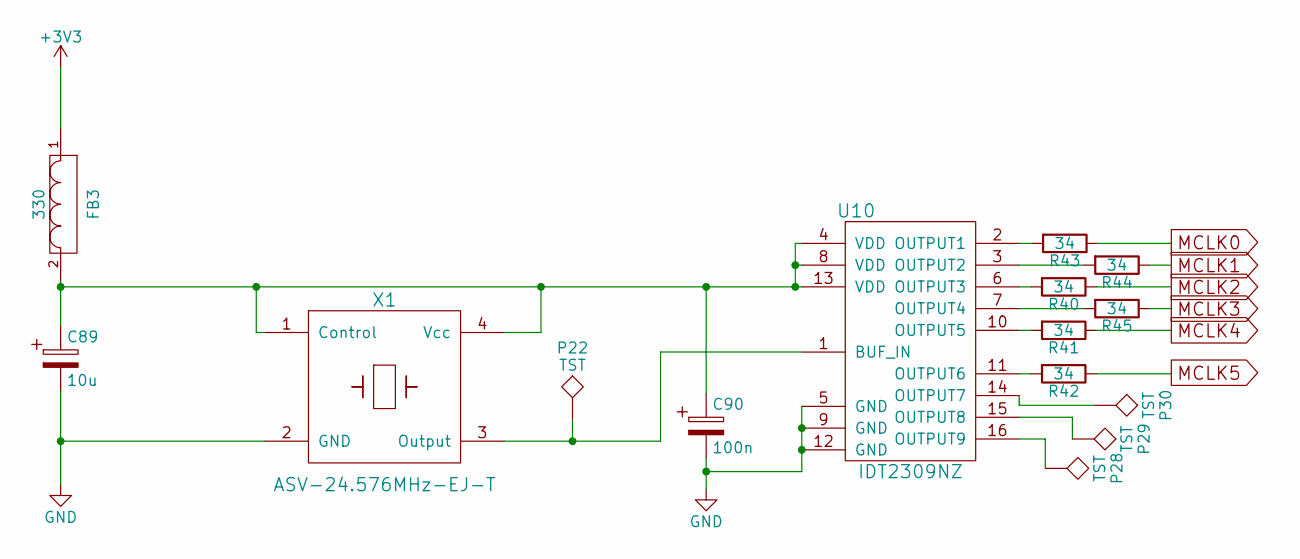
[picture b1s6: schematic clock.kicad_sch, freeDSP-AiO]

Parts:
C89: 10u; C_1206_HandSoldering
C90: 100n; C_1206_HandSoldering
FB3: 330; C_0805_HandSoldering
P22, P28, P29, P30: TST; Measurement_Point_Round-SMD-Pad_Small
R40, R41, R42, R43, R44, R45: 34; R_1206_HandSoldering
U10: IDT2309NZ; SOIC-16_3.9x9.9mm_Pitch1.27mm
X1: ASV-24.576MHz-EJ-T; Oscillator_SMD_Abracon_ASV-4pin_7.0x5.1mm_HandSoldering

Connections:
+3V3: FB3.1; also elsewhere on the board
GND: C89.2, C90.2, U10.5 (GND), U10.9 (GND), U10.12 (GND), X1.2 (GND); also elsewhere on the board
MCLK0: R43.1; also elsewhere on the board
MCLK1: R44.1; also elsewhere on the board
MCLK2: R40.1; also elsewhere on the board
MCLK3: R45.1; also elsewhere on the board
MCLK4: R41.1; also elsewhere on the board
MCLK5: R42.1; also elsewhere on the board
unnamed: P22.1, U10.1 (BUF_IN), X1.3 (Output)
unnamed: R43.2, U10.2 (OUTPUT1)
unnamed: R44.2, U10.3 (OUTPUT2)
unnamed: R40.2, U10.6 (OUTPUT3)
unnamed: R45.2, U10.7 (OUTPUT4)
unnamed: R41.2, U10.10 (OUTPUT5)
unnamed: R42.2, U10.11 (OUTPUT6)
unnamed: P30.1, U10.14 (OUTPUT7)
unnamed: P29.1, U10.15 (OUTPUT8)
unnamed: P28.1, U10.16 (OUTPUT9)
unnamed: C89.1, C90.1, FB3.2, U10.4 (VDD), U10.8 (VDD), U10.13 (VDD), X1.1 (Control), X1.4 (Vcc)

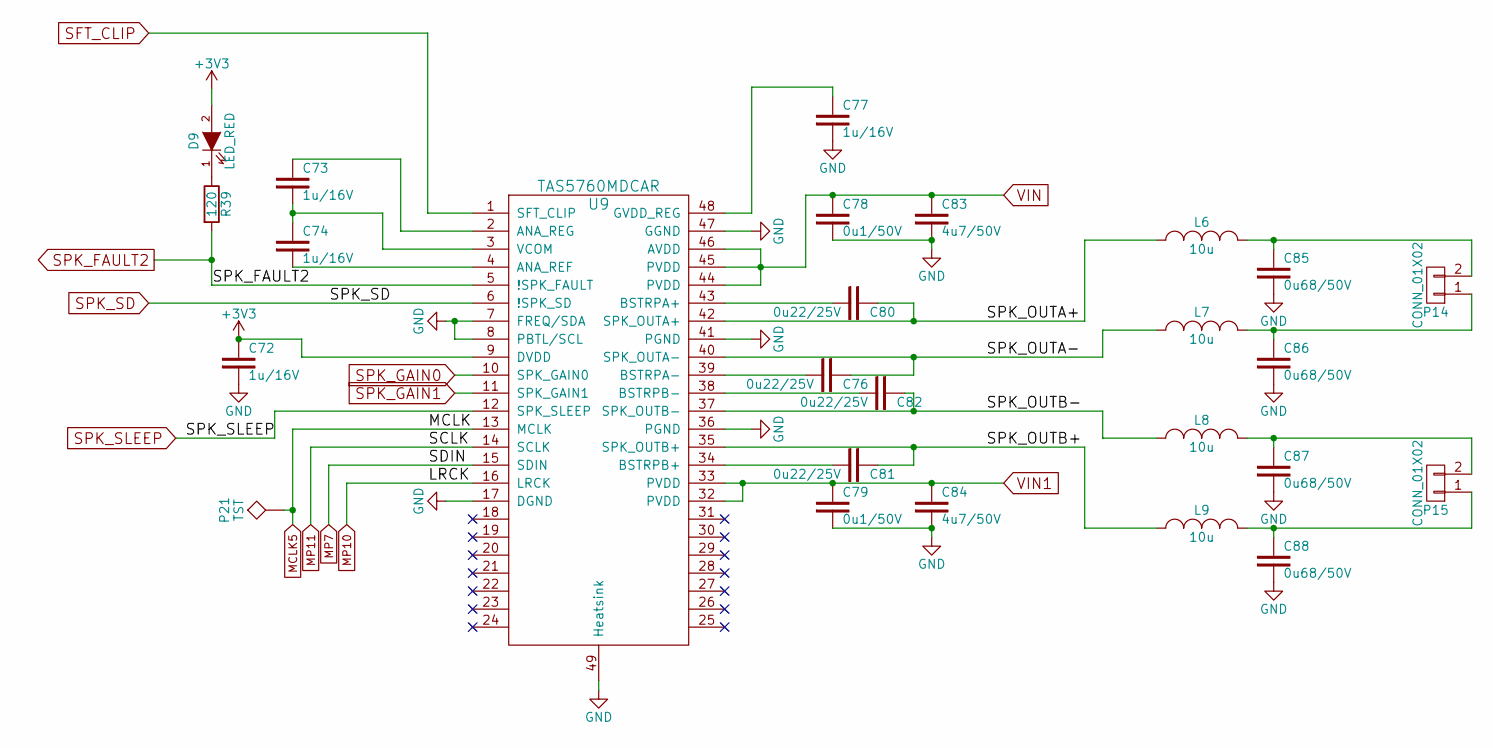
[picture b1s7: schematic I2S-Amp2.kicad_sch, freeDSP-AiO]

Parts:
C72, C73, C74, C77: 1u/16V; C_1206_HandSoldering
C76, C80, C81, C82: 0u22/25V; C_0805_HandSoldering
C78, C79: 0u1/50V; C_1206_HandSoldering
C83, C84: 4u7/50V; C_1206_HandSoldering
C85, C86, C87, C88: 0u68/50V; C_1206_HandSoldering
D9: LED_RED; R_1206_HandSoldering
L6, L7, L8, L9: 10u; 1D10ASeries
P14, P15: CONN_01X02; RIACON101-2
P21: TST; Measurement_Point_Round-SMD-Pad_Small
R39: 120; R_1206_HandSoldering
U9: TAS5760MDCAR; HTSSOP-48

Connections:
+3V3: C72.1, D9.2 (A), U9.9 (DVDD); also elsewhere on the board
/AMPx2_2/SPK_OUTA+: C80.1, L6.1, U9.42 (SPK_OUTA+)
/AMPx2_2/SPK_OUTA-: C76.1, L7.1, U9.40 (SPK_OUTA-)
/AMPx2_2/SPK_OUTB+: C81.1, L9.1, U9.35 (SPK_OUTB+)
/AMPx2_2/SPK_OUTB-: C82.1, L8.1, U9.37 (SPK_OUTB-)
GND: C72.2, C77.2, C78.2, C79.2, C83.2, C84.2, C85.2, C86.2, C87.2, C88.2, U9.7 (FREQ/SDA), U9.8 (PBTL/SCL), U9.17 (DGND), U9.36 (PGND), U9.41 (PGND), U9.47 (GGND), U9.49 (Heatsink); also elsewhere on the board
MCLK5: P21.1, U9.13 (MCLK); also elsewhere on the board
MP7: U9.15 (SDIN); also elsewhere on the board
MP10: U9.16 (LRCK); also elsewhere on the board
MP11: U9.14 (SCLK); also elsewhere on the board
unnamed: D9.1 (K), R39.1
unnamed: C86.1, L7.2, P14.1
unnamed: C85.1, L6.2, P14.2
unnamed: C88.1, L9.2, P15.1
unnamed: C87.1, L8.2, P15.2
unnamed: C74.2, U9.4 (ANA_REF)
unnamed: C73.1, U9.2 (ANA_REG)
unnamed: C80.2, U9.43 (BSTRPA+)
unnamed: C76.2, U9.39 (BSTRPA-)
unnamed: C81.2, U9.34 (BSTRPB+)
unnamed: C82.2, U9.38 (BSTRPB-)
unnamed: C77.1, U9.48 (GVDD_REG)
unnamed: C73.2, C74.1, U9.3 (VCOM)
SFT_CLIP: U9.1 (SFT_CLIP); also elsewhere on the board
SPK_FAULT2: R39.2, U9.5 (!SPK_FAULT); also elsewhere on the board
SPK_GAIN0: U9.10 (SPK_GAIN0); also elsewhere on the board
SPK_GAIN1: U9.11 (SPK_GAIN1); also elsewhere on the board
SPK_SD: U9.6 (!SPK_SD); also elsewhere on the board
SPK_SLEEP: U9.12 (SPK_SLEEP); also elsewhere on the board
VIN: C78.1, C83.1, U9.44 (PVDD), U9.45 (PVDD), U9.46 (AVDD); also elsewhere on the board
VIN1: C79.1, C84.1, U9.32 (PVDD), U9.33 (PVDD); also elsewhere on the board

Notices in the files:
parts and their libraries:
Copyright 2016 Accelerated Designs. All rights reserved.
